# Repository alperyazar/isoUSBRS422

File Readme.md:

# isoUSBRS422

Links:

|               |               |
| ------------- |-------------|
| Up-to-date BOM (with price) | [https://octopart.com/bom-tool/p8YATXJo](https://octopart.com/bom-tool/p8YATXJo) |
| Known Issues | [https://github.com/alperyazar/isoUSBRS422/issues](https://github.com/alperyazar/isoUSBRS422/issues)
| Photo Gallery | [https://www.flickr.com/photos/134583834@N07/sets/72157658466808770/](https://www.flickr.com/photos/134583834@N07/sets/72157658466808770/) |
| Hackaday.io | [https://hackaday.io/project/3943-isousbrs422](https://hackaday.io/project/3943-isousbrs422) |
| Project Page on My Website (may contain additional materials) | [https://www.ayazar.com/projects/isousbrs422.html](https://www.ayazar.com/projects/isousbrs422.html) |

> :information_source: isoUSBRS422v1 is on **EEVblog Mailbag** and **Dangerous Prototypes.** See [On The Web](#on-the-web) section at the bottom for details.

isoUSBRS422 is an **isolated** USB <-> RS422/RS485 converter board (~5x5 cm). It should work with Windows, Linux and MacOSX (not fully tested for all operating systems by me).

**THIS PROJECT IS PUBLISHED UNDER CC BY-NC-SA 4.0 LICENSE**

**AS IS, ABSOLUTELY NO WARRANTY**

## Features

Here is the summary of features in “catalog” style:

*Summary of isoUSBRS422 features*

Here is the introduction video:

")

* **Isolated** 5000 Vrms (IC specification, not tested by me)
* **4 different modes** RS-422, RS-485 4-wire, RS-485 2-wire, RS-485 2-wire w/echo suppression
* **5 cm x 5 cm, 2-layers PCB**
* **4 x 2.7 mm diameter mounting holes** Electrically floating
* **Baud Rate: 300 bps - 3 Mbps** Baud Rate = 3000000 / (n + x) where ‘n’ can be any integer between 2 and 16,384 and ‘x’ can be a sub-integer of the value 0, 0.125, 0.25, 0.375, 0.5, 0.625, 0.75, or 0.875. When n = 1, x = 0, i.e. baud rate divisors with values between 1 and 2 are not possible.
* **Powered from USB port** No external power supply is required. 5V from USB port is sufficient to operate the device.
* **USB overcurrent protection** Yes, by a polyfuse
* **RS-422/RS-485 line protection** Yes, it should meet IEC 61000-4-2, 61000-4-4 and IEC 61000-4-5 (IC specification, not tested by me)
* Supported OS: **Windows, Linux, MacOSX**
* **Various termination options** Different termination topologies can be selected by changing some passives on the component side using solder and iron! (Sorry, no dip switches)
* **Screw terminals for RS-422/RS-485 side**
* **LED indicators: Power, Transmit, Receive**

## What is isoUSBRS422?

As I said, basically it is an USB ↔ RS-422/RS-485 converter board. It can be used to communicate devices with RS-422/RS-485 interface by using a USB port of PC. Also, ground of USB port is isolated from ground of RS-422/RS-485 channel. It may help you to prevent [ground loops](https://en.wikipedia.org/wiki/Ground_loop_%28electricity%29) in large systems. See [Galvanic isolation](https://en.wikipedia.org/wiki/Galvanic_isolation) for further explanation. I will explain technical details later.

isoUSBRs422 is my first open source hardware and also KiCad experience. I did some boards for my daily job previously, but I never published them in public domain. So, I decided to do "something" to gain experience about open source publishing and low cost PCB production. Here there are some photos:

## Why

### Why did I design an isolated USB ↔ RS-422/RS-485 converter board?

As I explained previously, I wanted to design and publish "something". I use USB ↔ RS-422 converter devices for my daily job heavily. I checked PCB manufacturers and decided to try Dirtypcbs. Dimension limit for the cheapest option is 5 cm x 5 cm and I decided to stick to this limit. I thought that I can design an isolated USB <-> RS-422 converter board within in this size limit and use it for my daily job. So I did it.

### Why did I chose the name isoUSBRS422? Does this board support RS-485 in addition to RS-422, right?

Yes, it supports both protocols. My initial goal was designing an isolated USB ↔ RS-422 converter board. Because I use RS-422 mainly not RS-485. However after design I noticed that it can also be used as an RS-485 converter. Also a name like *isoUSBRS422-485* is quite long for a board name.

### Why did I use KiCad?

Couple of years ago, I designed 3 different boards for my project design course in collage using DipTrace. DipTrace is great and I would continue to use it if I didn’t decide to publish my project and make it open source. DipTrace has *freeware* version for non-commercial users. However, this version has limitation on number of total pins on a single PCB. I think that software used for an open source project should be free (as in beer and freedom) as much as possible. Also, I had to create some parts in library for this project. If I use DipTrace, later I may hit the pin limit for my other projects and I have to move another software. For these reasons, I eliminate Eagle. I think that, it is easier to learn and use DipTrace than Eagle.

From *free* PCB design softwares, I tried gEDA and KiCad. I encountered some stability issues in gEDA then I selected to use KiCad. This is my first KiCad and experience and now I am happy with my decision. I recommend KiCad. It has quite good documentation and there are great videos on YouTube explaining almost all aspects of the software. Also there are active helping forums on the internet.

### Why the heck did I select a USB chip from FTDI? Don’t I know that they did stupid things in the past? Am I supporting them?

Yes, I know and I am not an FTDI fanboy. For those who don’t know the subject:

and

[http://hackaday.com/2014/10/22/watch-that-windows-update-ftdi-drivers-are-killing-fake-chips/](http://hackaday.com/2014/10/22/watch-that-windows-update-ftdi-drivers-are-killing-fake-chips/)

started to desing and selected to components prior to FTDI thing. I learned the issue in the beginning of the layout. I was very excited to finish my board and decided to finish it. So, that’s the story. Now, I can’t proudly say that “Hey, I am using an FTDI chip on my board”. I know that, many of hackers and makers encountered problems due to stupidity of this company. Since this is an open source project and aims makers especially, I am not very happy with this chip. But this is the case.

## Do It Yourself (DIY)

> :warning: AS IS, ABSOLUTELY NO WARRANTY. TAKE YOUR OWN RISK

Your read the features list and are fascinated about the project (LOL). You look forward to make your own isoUSBRS422 board and use it in your projects. Here is the good new: This is an open source project and you can make your own copy for non-commercial purposes!

> :information_source: This project is published under CC BY-NC-SA 4.0 license. It means that you can make your own copy for non-commercial purposes. Even, you can modify the project files, ex. PCB, if you refer to this original work properly and redistribute your version with the same license. See [https://creativecommons.org/licenses/by-nc-sa/4.0/](https://creativecommons.org/licenses/by-nc-sa/4.0/) for further details. Contact if you have any questions.

> :information_source: As I said in videos (see below), I may have some extra PCBs or even components in my hand. I may able to send you if you REALLY want to make your own board, free of charge. Please contact if you are interested in.

## Video Tutorials

I prepared 6 tutorial videos with total runtime ~1.5 hours (!) for makers. Below, videos are given in order. Click images to watch the videos. Also you can find a ordered playlist here: [https://www.youtube.com/watch?v=EZh2zi6m1yI&list=PLr5LL6z9GIeGnNSeiEEnGr73dqn5cAOdi](https://www.youtube.com/watch?v=EZh2zi6m1yI&list=PLr5LL6z9GIeGnNSeiEEnGr73dqn5cAOdi)

### Part 0 - Introduction

")

*Click on the image to watch the video*

### Part 1 - Features

")

*Click on the image to watch the video*

### Part 2 - Project Files

")

*Click on the image to watch the video*

### Part 3 - Board Production

")

*Click on the image to watch the video*

### Part 4 - Driver Installation, Programming, Functional Verification

")

*Click on the image to watch the video*

### Part 5 - Operation Modes

")

*Click on the image to watch the video*

### Part 6 - Known Issues

")

*Click on the image to watch the video*

## On The Web

isoUSBRS422 project is also shown up on some websites.

### Dangerous Prototypes

[Blog post of Dangerous Prototypes about isoUSBRS422 project](http://dangerousprototypes.com/2015/12/17/isousbrs422-an-open-source-isolated-usb-rs422rs485-converter-board/)

### EEVblog

*Click on the image to watch the video*

isoUSBRS422v1 board is shown up in [EEVblog #833 - Mailbag](https://www.youtube.com/watch?time_continue=822&v=dXbbJOH59oo) episode between **13:42 - 18:26**.

## Folder Structure

* `BOM` Contains bill of materials of board

* `Driver` Contains necessary drivers. Online Windows 7 (and probably newest versions) should install driver automatically. If you are running on an offline machine you may use drivers at that folder. However, I strongly recommend to get the newest driver from USB chip vendor website: [http://www.ftdichip.com/Drivers/VCP.htm](http://www.ftdichip.com/Drivers/VCP.htm) I won't update drivers at that folder when FTDI publishes new drivers. They are latest drivers at that time.

* `Firmware` Contains profile file for utility called FT_Prog (contains in Utility folder). Once you finish isoUSBRS422 board, FT230x will not work as RS422/RS485 converter. This chip should be programmed only once. You may use the given profiles for proper operation.

* `Gerber` Contains Gerber files for PCB production. You may produce exactly same board as mine using these files.

* `KiCad` Contains KiCad project files. My KiCad version is (2013-07-07 BZR 4022)-stable. You should able to open project files and edit according to your needs (please consider license).

* `PCB` Contains ZofzPCB (see: [https://www.ayazar.com/log/2014/12/zofzpcb.html](https://www.ayazar.com/log/2014/12/zofzpcb.html)) rendered board file and some computer generated images of PCB.

* `Schematic` Contains PDF of schematic.

* `Utility` Some programs to program isoUSBRS422 board an test it.

*You are always welcomed to contact me.*

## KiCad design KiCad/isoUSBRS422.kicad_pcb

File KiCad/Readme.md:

# KiCad

Tested KiCad Version: (2013-07-07 BZR 4022)-stable on Windows 7 SP1

*1544*

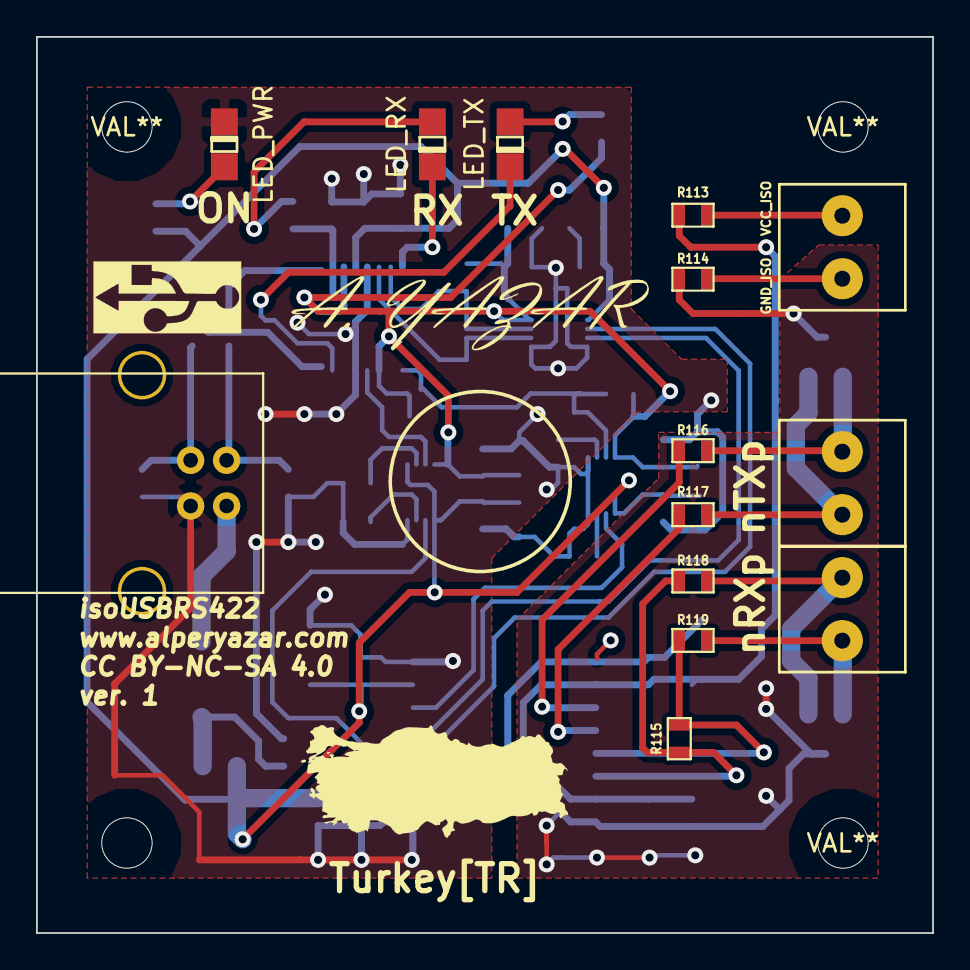
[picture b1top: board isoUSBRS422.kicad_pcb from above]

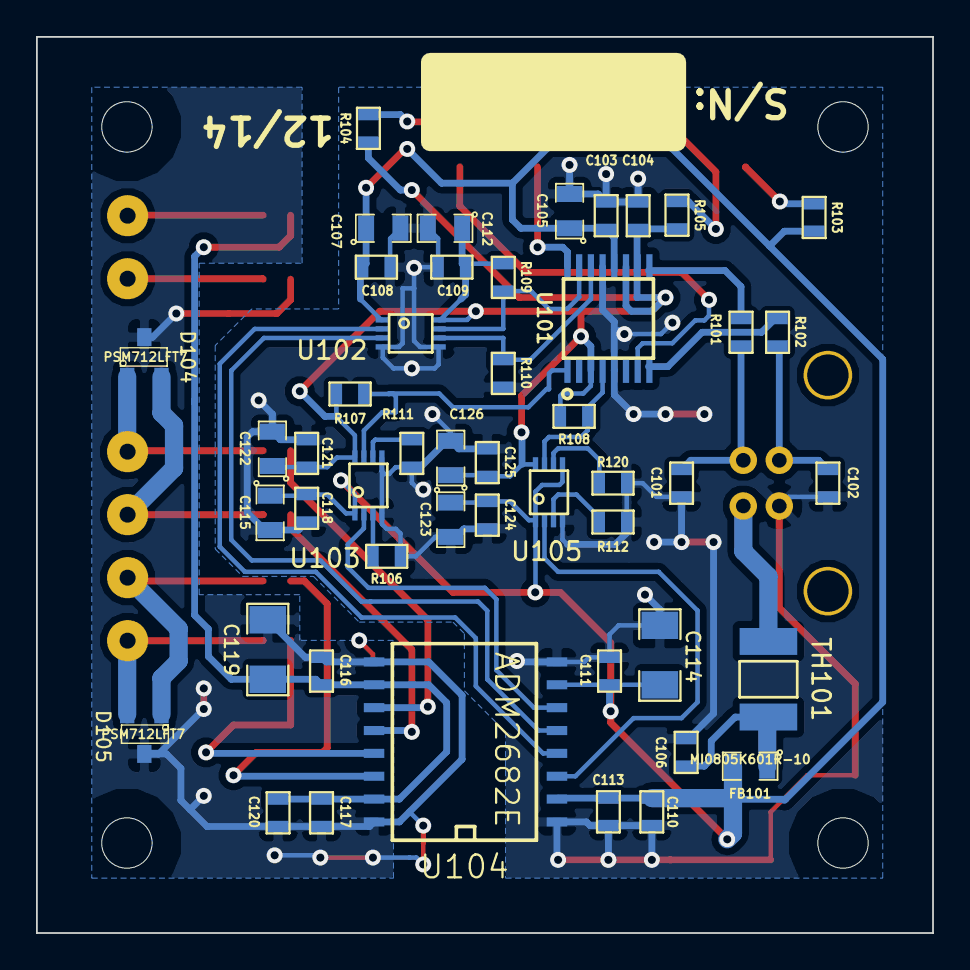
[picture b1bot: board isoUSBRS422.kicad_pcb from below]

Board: 2 copper layers, 49.8 x 49.8 mm, 69 parts (48 on the bottom side), 38 nets.

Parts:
C101, C102: 47 pF; SM0603
C103, C104, C108, C109, C110, C111, C116, C118, C120, C121, C124, C125: 100 nF; SM0603
C105, C107, C112, C115, C122, C123, C126: 4.7 uF; SM0805
C106, C113, C117: 10 nF; SM0603
C114, C119: 10 uF; SM1206
D101: LED_PWR; CR_10_LED
D102: LED_TX; CR_10_LED
D103: LED_RX; CR_10_LED
D104, D105: PSM712LFT7; SOT23
FB101: MI0805K601R-10; SM0805
Hole_2mm8_6mm0, Hole_2mm8_6mm0#2, Hole_2mm8_6mm0#3, Hole_2mm8_6mm0#4: VAL**; Hole_2mm8_6mm0
J101: USB; USB_B
J102, J103, J104: KLE3MM5; KLE3mm5
R101, R102: 27; SM0603
R103: 330; SM0603
R104, R105: 270; SM0603
R106, R107, R108, R109, R110, R111, R112, R120: 10k; SM0603
R113, R114, R116, R117, R118, R119: 0; SM0603
R115: 121; SM0603
TH101: MF-MSMF050-2; MS_MSMF_Style_1
U101: FT230X; SSOP16
U102, U103, U105: SN74LVC2T45; R_PDSO_G8
U104: ADM2682E; SO16W
VAL: REF; ayazar
VAL#2: REF; usb_logo_4mm
VAL#3: REF; turkiye_15mm

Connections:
+3.3V: C104.1, C109.1, C112.1, C121.1, C122.1, C125.1, C126.1, R104.2, R105.2, R107.2, R108.2, R109.2, U101.3, U101.10, U101.11, U102.8, U103.8, U105.8
+5V: C103.1, C105.1, C107.1, C108.1, C110.1, C111.1, C113.1, C114.1, C115.1, C118.1, C123.1, C124.1, FB101.2, R103.2, U101.12, U102.1, U103.1, U104.2, U104.7, U105.1, U105.5
+5V_USB: J101.1, TH101.1
/DE_3v3: R110.2, U101.14, U102.6
/DE_5v: U102.3, U104.5
/RXn: D105.2, J104.2, R119.2
/RXp: D105.1, J104.1, R118.2
/RxD_3v3: R108.1, U101.4, U105.7
/RxD_5v: U104.3, U105.2
/TXn: D104.2, J103.2, R117.2
/TXp: D104.1, J103.1, R116.2
/TxD_3v3: R107.1, U101.1, U103.7
/TxD_5v: U103.2, U104.6
/USB_m: C101.1, J101.2, R101.1
/USB_p: C102.1, J101.3, R102.1
/nRE_3v3: R109.1, U101.15, U102.7
/nRE_5v: U102.2, U104.4
/nRxLED: D103.2, U101.16
/nTxLED: D102.2, U101.7
GND: C101.2, C102.2, C103.2, C104.2, C105.2, C106.2, C107.2, C108.2, C109.2, C110.2, C111.2, C112.2, C113.2, C114.2, C115.2, C118.2, C121.2, C122.2, C123.2, C124.2, C125.2, C126.2, D101.2, J101.4, R106.1, R110.1, R111.1, R112.1, R120.1, U101.5, U101.13, U102.4, U102.5, U103.4, U103.5, U104.1, U104.8, U105.4
GND_ISO: C116.2, C117.2, C119.2, C120.2, D104.3, D105.3, R114.1, U104.9, U104.16
unnamed: R106.2, U103.3
unnamed: R111.2, U103.6
unnamed: R112.2, U105.3
unnamed: R120.2, U105.6
unnamed: D101.1, R103.1
unnamed: D102.1, R104.1
unnamed: D103.1, R105.1
unnamed: R102.2, U101.8
unnamed: R101.2, U101.9
unnamed: J102.2, R114.2
unnamed: J102.1, R113.2
unnamed: R117.1, U104.12
unnamed: R116.1, U104.11
unnamed: R115.1, R119.1, U104.13
unnamed: R115.2, R118.1, U104.14
unnamed: C106.1, FB101.1, TH101.2
VCC_ISO: C116.1, C117.1, C119.1, C120.1, R113.1, U104.10, U104.15

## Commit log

2015-11-09 First commit of v1
2020-02-16 Moved project description from my personal site to here
2020-02-16 added eevblog video continue parameter
2020-02-16 modification to links table
2020-02-16 link table minor addition
2020-06-13 Change URLs
2021-04-22 Update Readme.md
    Update links to my personal site
